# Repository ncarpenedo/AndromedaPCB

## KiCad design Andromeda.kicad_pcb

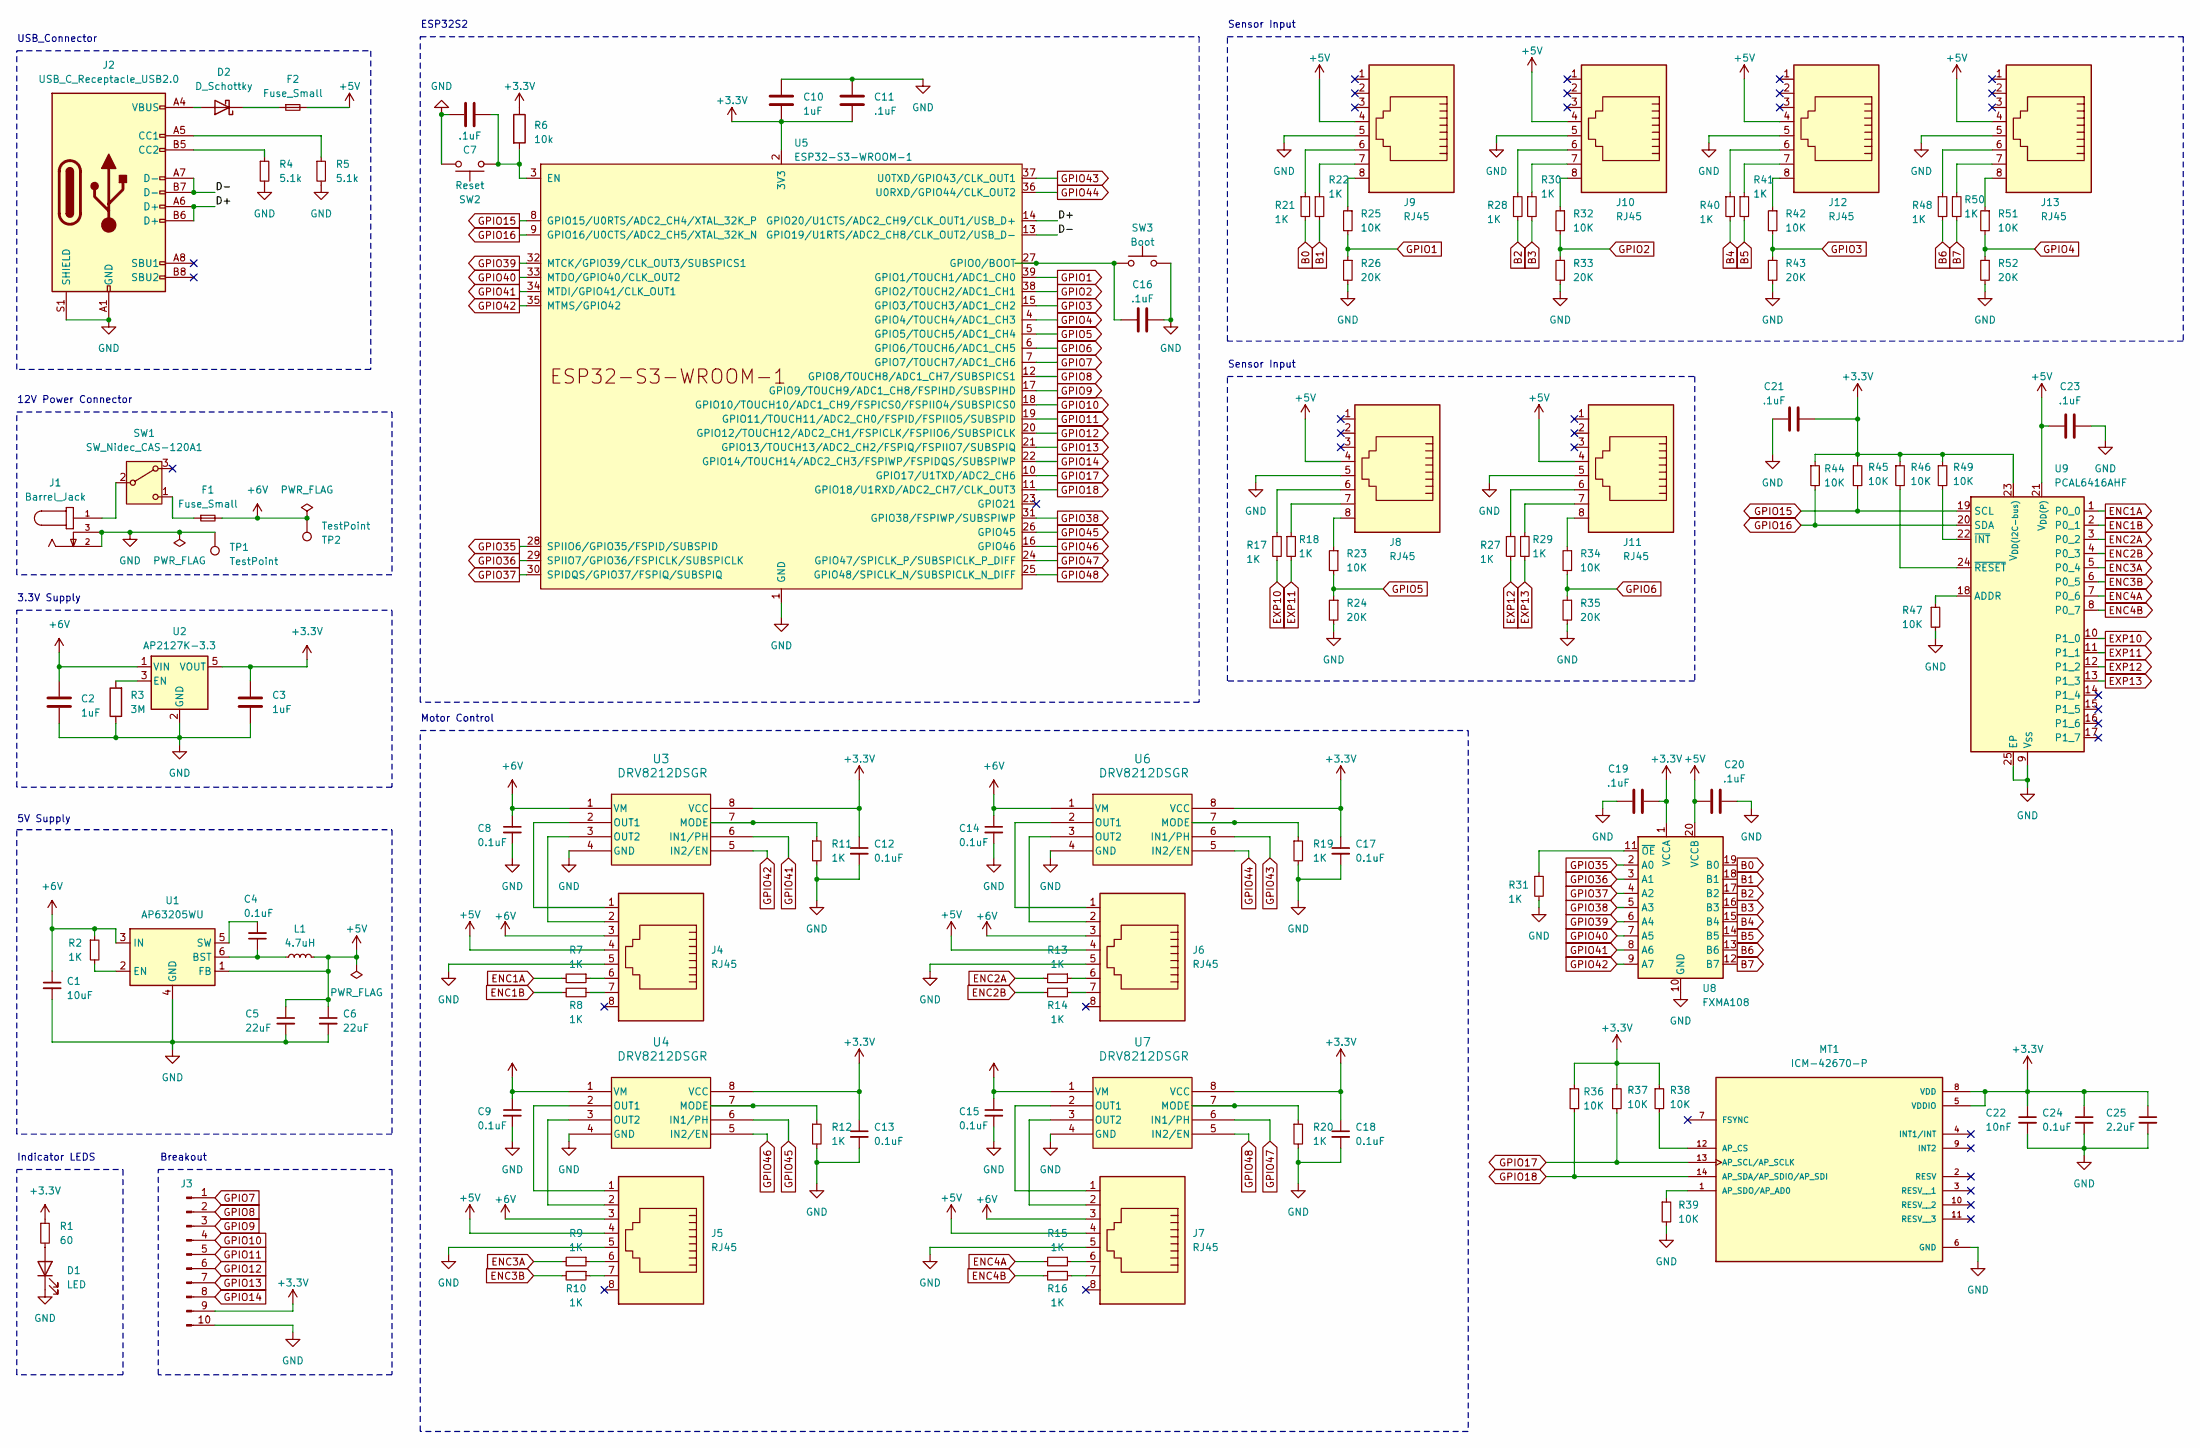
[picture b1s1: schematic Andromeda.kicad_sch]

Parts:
C1: 10uF; C_0805_2012Metric
C2, C3, C10: 1uF; C_0805_2012Metric
C4, C8, C9, C12, C13, C14, C15, C17, C18, C24: 0.1uF; C_0805_2012Metric
C5, C6: 22uF; C_0805_2012Metric
C7, C11, C16, C19, C20, C21, C23: .1uF; C_0805_2012Metric
C22: 10nF; C_0805_2012Metric
C25: 2.2uF; C_0805_2012Metric
D1: LED; D_1206_3216Metric
D2: D_Schottky; D_SMC
F1, F2: Fuse_Small; Fuse_0805_2012Metric
J1: Barrel_Jack; CUI_PJ-036AH-SMT-TR; DIGI-KEY_PART_NUMBER CP-036AHPJCT-ND
J2: USB_C_Receptacle_USB2.0; USB_C_Receptacle_JAE_DX07S016JA1R1500
J3: Conn_01x10_Pin; PinHeader_1x10_P2.54mm_Vertical
J4, J5, J6, J7, J8, J9, J10, J11, J12, J13: RJ45; RJ45_Amphenol_54602-x08_Horizontal
L1: 4.7uH; L_Radial_D9.5mm_P5.00mm_Fastron_07HVP
MT1: ICM-42670-P; XDCR_ICM-42670-P; PARTREV 1.1
R1: 60; R_0805_2012Metric
R2, R7, R8, R9, R10, R11, R12, R13, R14, R15, R16, R17, R18, R19, R20, R21, R22, R27, R28, R29, R30, R31, R40, R41, R48, R50: 1K; R_0805_2012Metric
R3: 3M; R_0805_2012Metric
R4, R5: 5.1k; R_0805_2012Metric
R6: 10k; R_0805_2012Metric
R23, R25, R32, R34, R36, R37, R38, R39, R42, R44, R45, R46, R47, R49, R51: 10K; R_0805_2012Metric
R24, R26, R33, R35, R43, R52: 20K; R_0805_2012Metric
SW1: SW_Nidec_CAS-120A1; Nidec_Copal_CAS-120A
SW2: Reset; SW_Push_1P1T_NO_6x6mm_H9.5mm
SW3: Boot; SW_Push_1P1T_NO_6x6mm_H9.5mm
TP1, TP2: TestPoint; TestPoint_Plated_Hole_D3.0mm
U1: AP63205WU; TSOT-23-6
U2: AP2127K-3.3; SOT-23-5
U3, U4, U6, U7: DRV8212DSGR; WSON_212DSGR_TEX
U5: ESP32-S3-WROOM-1
U8: FXMA108; WQFN-20-1EP_2.5x4.5mm_P0.5mm_EP1x2.9mm
U9: PCAL6416AHF; HVQFN-24-1EP_4x4mm_P0.5mm_EP2.1x2.1mm

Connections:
+3.3V: C3.1, C10.2, C11.2, C12.1, C13.1, C17.1, C18.1, C19.1, C21.1, C22.1, C24.1, C25.1, J3.9, MT1.5 (VDDIO), MT1.8 (VDD), R1.1, R6.1, R36.1, R37.1, R38.1, R44.1, R45.1, R46.1, R49.1, U2.5 (VOUT), U3.8 (VCC), U4.8 (VCC), U5.2 (3V3), U6.8 (VCC), U7.8 (VCC), U8.1 (VCCA), U9.23 (V_{DD(I2C-bus)})
+5V: C5.1, C6.1, C20.2, C23.2, F2.2, J4.4, J5.4, J6.4, J7.4, J8.4, J9.4, J10.4, J11.4, J12.4, J13.4, L1.2, U1.1 (FB), U8.20 (VCCB), U9.21 (V_{DD(P)})
+6V: C1.1, C2.1, C8.1, C9.1, C14.1, C15.1, F1.2, J4.3, J5.3, J6.3, J7.3, R2.1, TP2.1, U1.3 (IN), U2.1 (VIN), U3.1 (VM), U4.1 (VM), U6.1 (VM), U7.1 (VM)
/D+: J2.A6 (D+), J2.B6 (D+), U5.14 (GPIO20/U1CTS/ADC2_CH9/CLK_OUT1/USB_D+)
/D-: J2.A7 (D-), J2.B7 (D-), U5.13 (GPIO19/U1RTS/ADC2_CH8/CLK_OUT2/USB_D-)
B0: R21.2, U8.19 (B0)
B1: R22.2, U8.18 (B1)
B2: R28.2, U8.17 (B2)
B3: R30.2, U8.16 (B3)
B4: R40.2, U8.15 (B4)
B5: R41.2, U8.14 (B5)
B6: R48.2, U8.13 (B6)
B7: R50.2, U8.12 (B7)
ENC1A: R7.2, U9.1 (P0_0)
ENC1B: R8.2, U9.2 (P0_1)
ENC2A: R13.2, U9.3 (P0_2)
ENC2B: R14.2, U9.4 (P0_3)
ENC3A: R9.2, U9.5 (P0_4)
ENC3B: R10.2, U9.6 (P0_5)
ENC4A: R15.2, U9.7 (P0_6)
ENC4B: R16.2, U9.8 (P0_7)
EXP10: R17.2, U9.10 (P1_0)
EXP11: R18.2, U9.11 (P1_1)
EXP12: R27.2, U9.12 (P1_2)
EXP13: R29.2, U9.13 (P1_3)
GND: C1.2, C2.2, C3.2, C5.2, C6.2, C7.1, C8.2, C9.2, C10.1, C11.1, C12.2, C13.2, C14.2, C15.2, C16.2, C17.2, C18.2, C19.2, C20.1, C21.2, C22.2, C23.1, C24.2, C25.2, D1.1 (K), J1.2, J1.3, J2.A1 (GND), J2.A12 (GND), J2.B1 (GND), J2.B12 (GND), J2.S1 (SHIELD), J3.10, J4.5, J5.5, J6.5, J7.5, J8.5, J9.5, J10.5, J11.5, J12.5, J13.5, MT1.6 (GND), R3.1, R4.2, R5.2, R11.2, R12.2, R19.2, R20.2, R24.2, R26.2, R31.2, R33.2, R35.2, R39.2, R43.2, R47.2, R52.2, SW2.1, SW3.2, TP1.1, U1.4 (GND), U2.2 (GND), U3.4 (GND), U4.4 (GND), U5.1 (GND), U5.40 (GND), U5.41 (GND), U6.4 (GND), U7.4 (GND), U8.10 (GND), U9.9 (V_{SS}), U9.25 (EP)
GPIO1: R25.2, R26.1, U5.39 (GPIO1/TOUCH1/ADC1_CH0)
GPIO2: R32.2, R33.1, U5.38 (GPIO2/TOUCH2/ADC1_CH1)
GPIO3: R42.2, R43.1, U5.15 (GPIO3/TOUCH3/ADC1_CH2)
GPIO4: R51.2, R52.1, U5.4 (GPIO4/TOUCH4/ADC1_CH3)
GPIO5: R23.2, R24.1, U5.5 (GPIO5/TOUCH5/ADC1_CH4)
GPIO6: R34.2, R35.1, U5.6 (GPIO6/TOUCH6/ADC1_CH5)
GPIO7: J3.1, U5.7 (GPIO7/TOUCH7/ADC1_CH6)
GPIO8: J3.2, U5.12 (GPIO8/TOUCH8/ADC1_CH7/SUBSPICS1)
GPIO9: J3.3, U5.17 (GPIO9/TOUCH9/ADC1_CH8/FSPIHD/SUBSPIHD)
GPIO10: J3.4, U5.18 (GPIO10/TOUCH10/ADC1_CH9/FSPICS0/FSPIIO4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)
GPIO11: J3.5, U5.19 (GPIO11/TOUCH11/ADC2_CH0/FSPID/FSPIIO5/S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)
GPIO12: J3.6, U5.20 (GPIO12/TOUCH12/ADC2_CH1/FSPICLK/FSPIIO6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)
GPIO13: J3.7, U5.21 (GPIO13/TOUCH13/ADC2_CH2/FSPIQ/FSPIIO7/S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)
GPIO14: J3.8, U5.22 (GPIO14/TOUCH14/ADC2_CH3/FSPIWP/FSPIDQS/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)
GPIO15: R45.2, U5.8 (GPIO15/U0RTS/ADC2_CH4/XTAL_32K_P), U9.19 (SCL)
GPIO16: R44.2, U5.9 (GPIO16/U0CTS/ADC2_CH5/XTAL_32K_N), U9.20 (SDA)
GPIO17: MT1.13 (AP_SCL/AP_SCLK), R37.2, U5.10 (GPIO17/U1TXD/ADC2_CH6)
GPIO18: MT1.14 (AP_SDA/AP_SDIO/AP_SDI), R36.2, U5.11 (GPIO18/U1RXD/ADC2_CH7/CLK_OUT3)
GPIO35: U5.28 (SPIIO6/GPIO35/FSPID/SUBSPID), U8.2 (A0)
GPIO36: U5.29 (SPIIO7/GPIO36/FSPICLK/SUBSPICLK), U8.3 (A1)
GPIO37: U5.30 (SPIDQS/GPIO37/FSPIQ/SUBSPIQ), U8.4 (A2)
GPIO38: U5.31 (GPIO38/FSPIWP/SUBSPIWP), U8.5 (A3)
GPIO39: U5.32 (MTCK/GPIO39/CLK_OUT3/SUBSPICS1), U8.6 (A4)
GPIO40: U5.33 (MTDO/GPIO40/CLK_OUT2), U8.7 (A5)
GPIO41: U3.6 (IN1/PH), U5.34 (MTDI/GPIO41/CLK_OUT1), U8.8 (A6)
GPIO42: U3.5 (IN2/EN), U5.35 (MTMS/GPIO42), U8.9 (A7)
GPIO43: U5.37 (U0TXD/GPIO43/CLK_OUT1), U6.6 (IN1/PH)
GPIO44: U5.36 (U0RXD/GPIO44/CLK_OUT2), U6.5 (IN2/EN)
GPIO45: U4.6 (IN1/PH), U5.26 (GPIO45)
GPIO46: U4.5 (IN2/EN), U5.16 (GPIO46)
GPIO47: U5.24 (GPIO47/SPICLK_P/SUBSPICLK_P_DIFF), U7.6 (IN1/PH)
GPIO48: U5.25 (GPIO48/SPICLK_N/SUBSPICLK_N_DIFF), U7.5 (IN2/EN)
unnamed: D1.2 (A), R1.2
unnamed: D2.2 (A), J2.A4 (VBUS), J2.A9 (VBUS), J2.B4 (VBUS), J2.B9 (VBUS)
unnamed: D2.1 (K), F2.1
unnamed: J2.A5 (CC1), R5.1
unnamed: J2.B5 (CC2), R4.1
unnamed: J4.6, R7.1
unnamed: J4.7, R8.1
unnamed: J5.6, R9.1
unnamed: J5.7, R10.1
unnamed: J6.6, R13.1
unnamed: J6.7, R14.1
unnamed: J7.6, R15.1
unnamed: J7.7, R16.1
unnamed: J8.6, R17.1
unnamed: J8.7, R18.1
unnamed: J8.8, R23.1
unnamed: J9.6, R21.1
unnamed: J9.7, R22.1
unnamed: J9.8, R25.1
unnamed: J10.6, R28.1
unnamed: J10.7, R30.1
unnamed: J10.8, R32.1
unnamed: J11.6, R27.1
unnamed: J11.7, R29.1
unnamed: J11.8, R34.1
unnamed: J12.6, R40.1
unnamed: J12.7, R41.1
unnamed: J12.8, R42.1
unnamed: J13.6, R48.1
unnamed: J13.7, R50.1
unnamed: J13.8, R51.1
unnamed: MT1.12 (AP_CS), R38.2
unnamed: MT1.1 (AP_SDO/AP_AD0), R39.1
unnamed: F1.1, SW1.1 (C)
unnamed: C4.1, L1.1, U1.6 (BST)
unnamed: R2.2, U1.2 (EN)
unnamed: C4.2, U1.5 (SW)
unnamed: R3.2, U2.3 (EN)
unnamed: R11.1, U3.7 (MODE)
unnamed: J4.1, U3.2 (OUT1)
unnamed: J4.2, U3.3 (OUT2)
unnamed: R12.1, U4.7 (MODE)
unnamed: J5.1, U4.2 (OUT1)
unnamed: J5.2, U4.3 (OUT2)
unnamed: C7.2, R6.2, SW2.2, U5.3 (EN)
unnamed: C16.1, SW3.1, U5.27 (GPIO0/BOOT)
unnamed: R19.1, U6.7 (MODE)
unnamed: J6.1, U6.2 (OUT1)
unnamed: J6.2, U6.3 (OUT2)
unnamed: R20.1, U7.7 (MODE)
unnamed: J7.1, U7.2 (OUT1)
unnamed: J7.2, U7.3 (OUT2)
unnamed: R31.1, U8.11 (~OE)
unnamed: R47.1, U9.18 (ADDR)
unnamed: R49.2, U9.22 (~INT)
unnamed: R46.2, U9.24 (~RESET)

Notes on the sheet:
5V Supply
Indicator LEDS
Motor Control
Sensor Input
Breakout
USB_Connector
ESP32S2
3.3V Supply
12V Power Connector

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
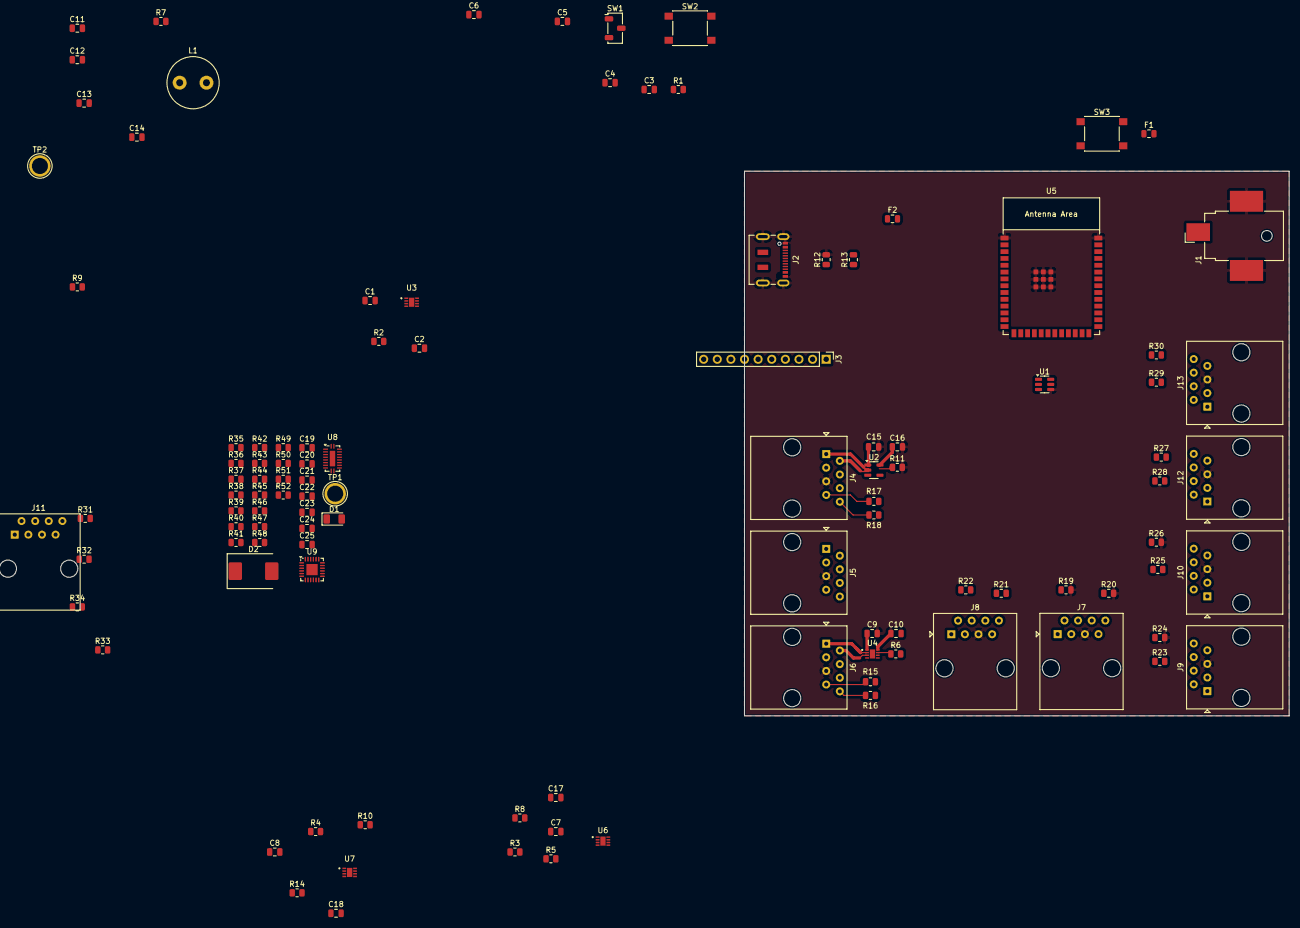
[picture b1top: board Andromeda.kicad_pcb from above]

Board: 2 copper layers, 101.6 x 101.6 mm, 109 parts (0 on the bottom side), 112 nets.

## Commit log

2024-04-17 Add kicad files
2024-04-18 Complete rough schematic
2024-04-19 Pass ERC
2024-04-19 Remove Logic Level Shifters
2024-04-19 Fix some weirdness
2024-04-19 Create NCD9830 symbol
2024-04-19 begin layout
2024-04-20 Switch to 5V, Add Gyro, GPIO extender
